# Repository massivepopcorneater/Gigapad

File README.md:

# Gigapad
A 9-key macropad that includes a LED for each key, a rotary encoder and a 0.91-inch OLED display. I made this project to challenge myself so that I can be better prepared to create real-world solutions and also I having a macropad with an OLED screen and a rotary encoder is pretty cool too. (Also for a soldering iron lol) 

Gigapad is a custom 9-key mechanical macropad built around the Seeed XIAO RP2040, featuring a rotary encoder and an OLED display.  
It is designed as a compact, programmable input device using QMK firmware, suitable for shortcuts, media control, and custom workflows.

---

## 🧱 Case & Assembly Fit

Made using Fusion 360 

Features:
- Easy access to the USB-C port
- Secured PCB and case using 4 M3 Screws with brass heatsets (2 on the case, 2 on the case and pcb)
- Different key levels for a more ergonomic feel

---

## 📐 Schematic

Made Using KiCad

The schematic shows:
- A 3×3 key matrix 
- A rotary encoder connected directly to GPIO pins 
- An OLED display
- 9 Mini-LED in series delivered using parallel power

---

## 🧩 PCB

The PCB is a 2-layer board designed for JLCPCB manufacturing with:
- 1 oz copper
- Dedicated encoder pins
- Ground pours and 5V pour

---

## 🧾 Bill of Materials (BOM)

| Part | Quantity | Description |
|----|----|----|
| Microcontroller | 1x | Seeed XIAO RP2040 |
| Mechanical Switches | 9x | MX-style switches |
| Keycaps | 9x | ABS Keycaps |
| Rotary Encoder | 1x | EC11 |
| OLED Display | 1x | 0.91-inch OLED Display |
| Diodes | 9x | 1N4148  |
| Brass Heat-Set Inserts | 4x | M3 |
| Screws | 4x | M3 × 16 mm |
| PCB | 1x | Custom 2-layer PCB |
| Case | 1x | 3D-printed enclosure |

---

## 💻 Firmware

Gigapad runs **QMK firmware**, configured for:
- 3×3 key matrix
- Rotary encoder using dedicated GPIO pins
- OLED display output
- Fully customizable keymap

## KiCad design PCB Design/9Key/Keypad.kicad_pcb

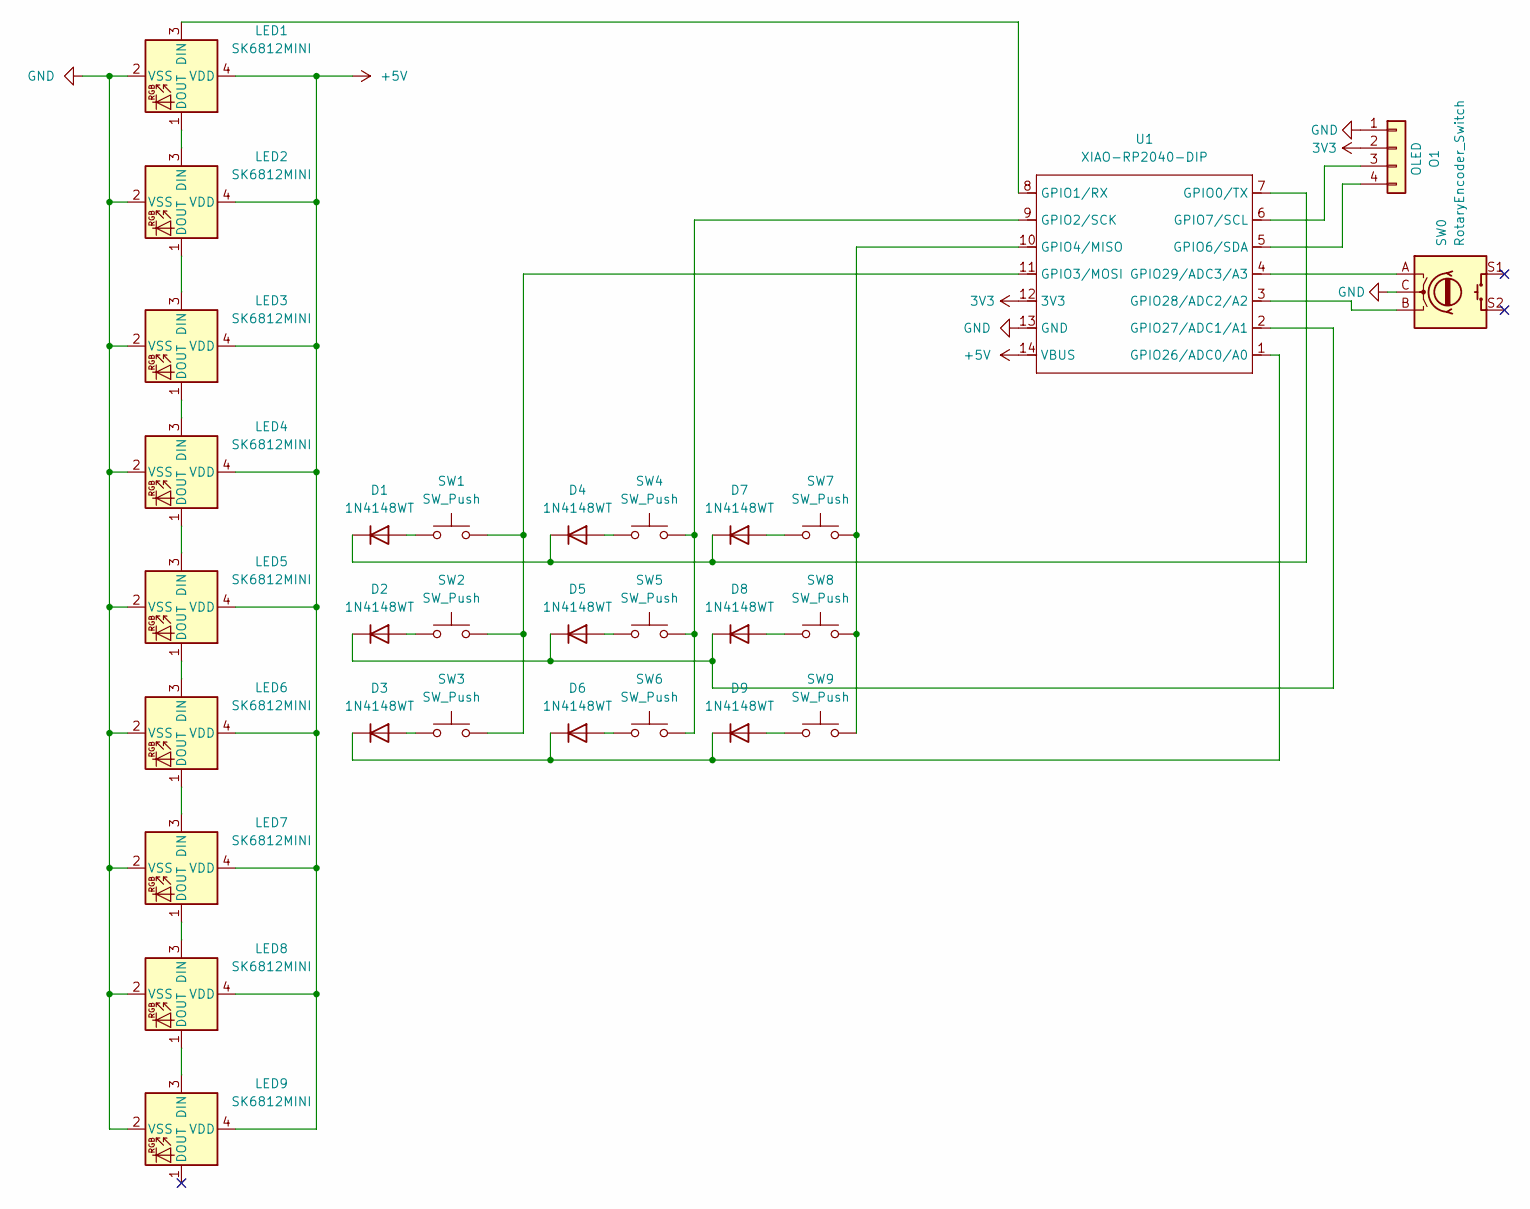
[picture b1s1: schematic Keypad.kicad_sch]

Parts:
D1, D2, D3, D4, D5, D6, D7, D8, D9: 1N4148WT; D_DO-35_SOD27_P7.62mm_Horizontal
LED1, LED2, LED3, LED4, LED5, LED6, LED7, LED8, LED9: SK6812MINI; LED_SK6812MINI_PLCC4_3.5x3.5mm_P1.75mm
O1: OLED; SSD1306-0.91-OLED-4pin-128x32
SW0: RotaryEncoder_Switch; RotaryEncoder_Alps_EC11E-Switch_Vertical_H20mm
SW1, SW2, SW3, SW4, SW5, SW6, SW7, SW8, SW9: SW_Push; SW_Cherry_MX_1.00u_PCB
U1: XIAO-RP2040-DIP

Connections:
3V3: O1.2, U1.12 (3V3)
+5V: LED1.4 (VDD), LED2.4 (VDD), LED3.4 (VDD), LED4.4 (VDD), LED5.4 (VDD), LED6.4 (VDD), LED7.4 (VDD), LED8.4 (VDD), LED9.4 (VDD), U1.14 (VBUS)
GND: LED1.2 (VSS), LED2.2 (VSS), LED3.2 (VSS), LED4.2 (VSS), LED5.2 (VSS), LED6.2 (VSS), LED7.2 (VSS), LED8.2 (VSS), LED9.2 (VSS), O1.1, SW0.C, U1.13 (GND)
unnamed: D1.2 (A), SW1.1
unnamed: D1.1 (K), D4.1 (K), D7.1 (K), U1.7 (GPIO0/TX)
unnamed: D2.2 (A), SW2.1
unnamed: D2.1 (K), D5.1 (K), D8.1 (K), U1.2 (GPIO27/ADC1/A1)
unnamed: D3.2 (A), SW3.1
unnamed: D3.1 (K), D6.1 (K), D9.1 (K), U1.1 (GPIO26/ADC0/A0)
unnamed: D4.2 (A), SW4.1
unnamed: D5.2 (A), SW5.1
unnamed: D6.2 (A), SW6.1
unnamed: D7.2 (A), SW7.1
unnamed: D8.2 (A), SW8.1
unnamed: D9.2 (A), SW9.1
unnamed: LED1.3 (DIN), U1.8 (GPIO1/RX)
unnamed: LED1.1 (DOUT), LED2.3 (DIN)
unnamed: LED2.1 (DOUT), LED3.3 (DIN)
unnamed: LED3.1 (DOUT), LED4.3 (DIN)
unnamed: LED4.1 (DOUT), LED5.3 (DIN)
unnamed: LED5.1 (DOUT), LED6.3 (DIN)
unnamed: LED6.1 (DOUT), LED7.3 (DIN)
unnamed: LED7.1 (DOUT), LED8.3 (DIN)
unnamed: LED8.1 (DOUT), LED9.3 (DIN)
unnamed: O1.3, U1.6 (GPIO7/SCL)
unnamed: O1.4, U1.5 (GPIO6/SDA)
unnamed: SW4.2, SW5.2, SW6.2, U1.9 (GPIO2/SCK)
unnamed: SW1.2, SW2.2, SW3.2, U1.11 (GPIO3/MOSI)
unnamed: SW7.2, SW8.2, SW9.2, U1.10 (GPIO4/MISO)
unnamed: SW0.B, U1.3 (GPIO28/ADC2/A2)
unnamed: SW0.A, U1.4 (GPIO29/ADC3/A3)

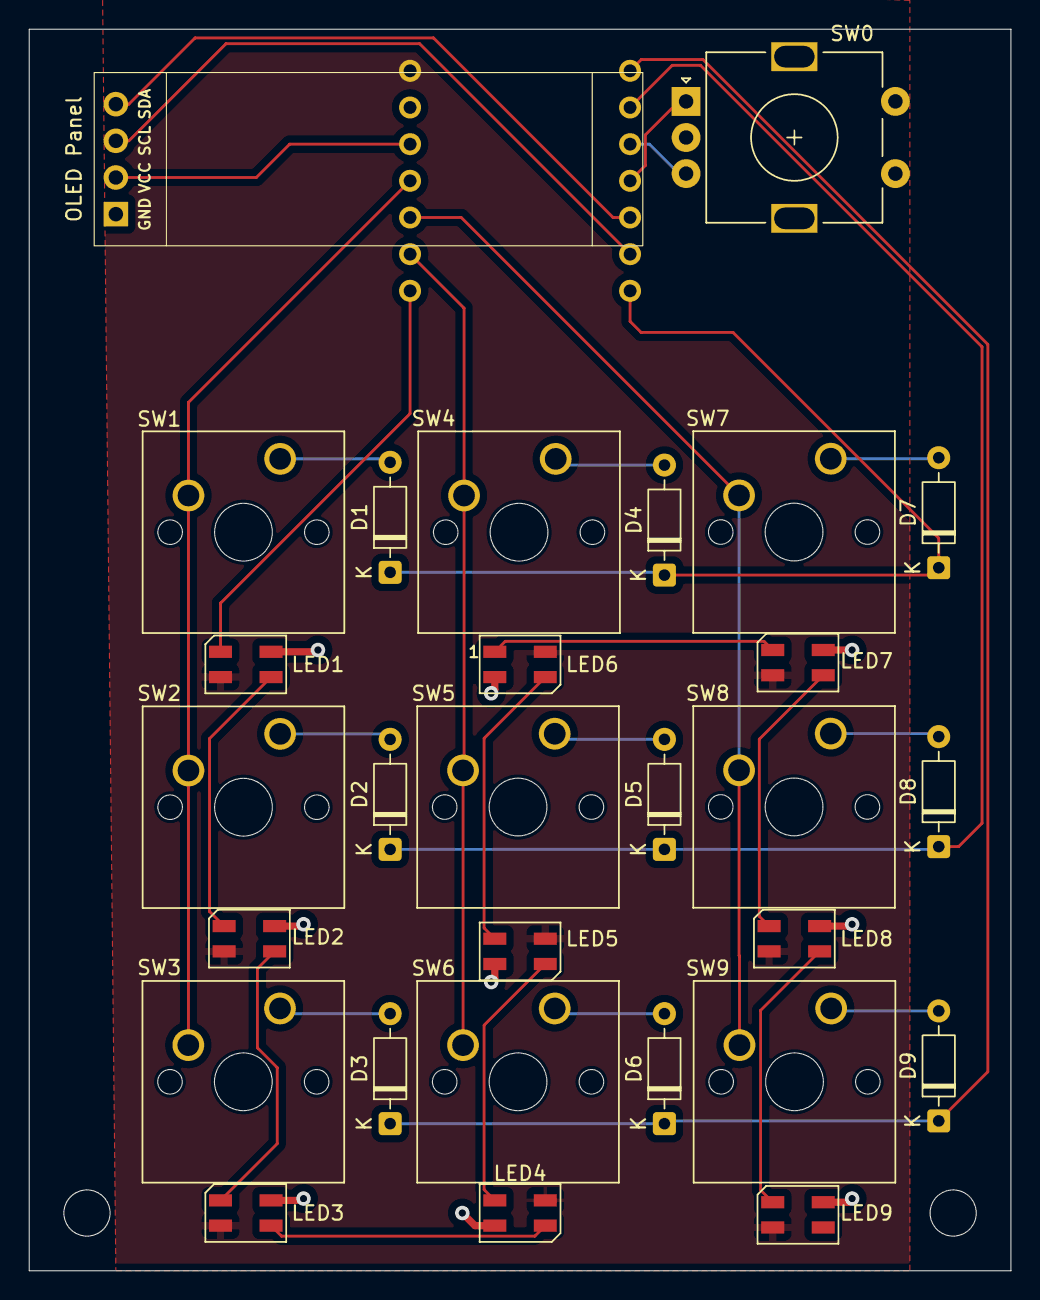
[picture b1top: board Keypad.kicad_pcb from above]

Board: 2 copper layers, 68.0 x 86.0 mm, 30 parts (1 on the bottom side), 31 nets.

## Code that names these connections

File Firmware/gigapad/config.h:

#pragma once

// ===== RGB Matrix (12x SK6812 MINI) =====
#define RGB_DI_PIN GP1
#define RGB_MATRIX_LED_COUNT 9

#define RGB_MATRIX_KEYPRESSES
#define RGB_DISABLE_WHEN_USB_SUSPENDED
#define RGB_MATRIX_MAXIMUM_BRIGHTNESS 180

// ===== Rotary encoder (dedicated pins, not in the key matrix) =====
// From your KiCad PCB: encoder A -> GPIO29 (A3), encoder B -> GPIO28 (A2)
#define ENCODERS_PAD_A { GP29 }
#define ENCODERS_PAD_B { GP28 }

// ===== OLED (SSD1306 over I2C) =====
// From your KiCad PCB: SDA -> GPIO6, SCL -> GPIO7
#define I2C1_SDA_PIN GP6
#define I2C1_SCL_PIN GP7
#define I2C1_CLOCK_SPEED 400000

// Most 0.96\" SSD1306 modules are 128x64; change to OLED_DISPLAY_128X32 if yours is 128x32.
#define OLED_DISPLAY_128X64

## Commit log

2026-02-05 Rename README.md to README.mdddd
2026-02-05 Rename README.mdddd to README.md
2026-02-05 File Name Change
2026-02-05 adding parts
2026-02-07 New PCB Format
2026-02-07 Assembly
2026-02-07 Readme update
2026-02-07 image
2026-02-07 firmware update
2026-02-07 images
2026-02-08 revision
2026-02-08 revision update
2026-02-16 schematic clean up
